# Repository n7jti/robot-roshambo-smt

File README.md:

# robot-roshambo-smt
the SMT board for Robot Rock Paper Scissors

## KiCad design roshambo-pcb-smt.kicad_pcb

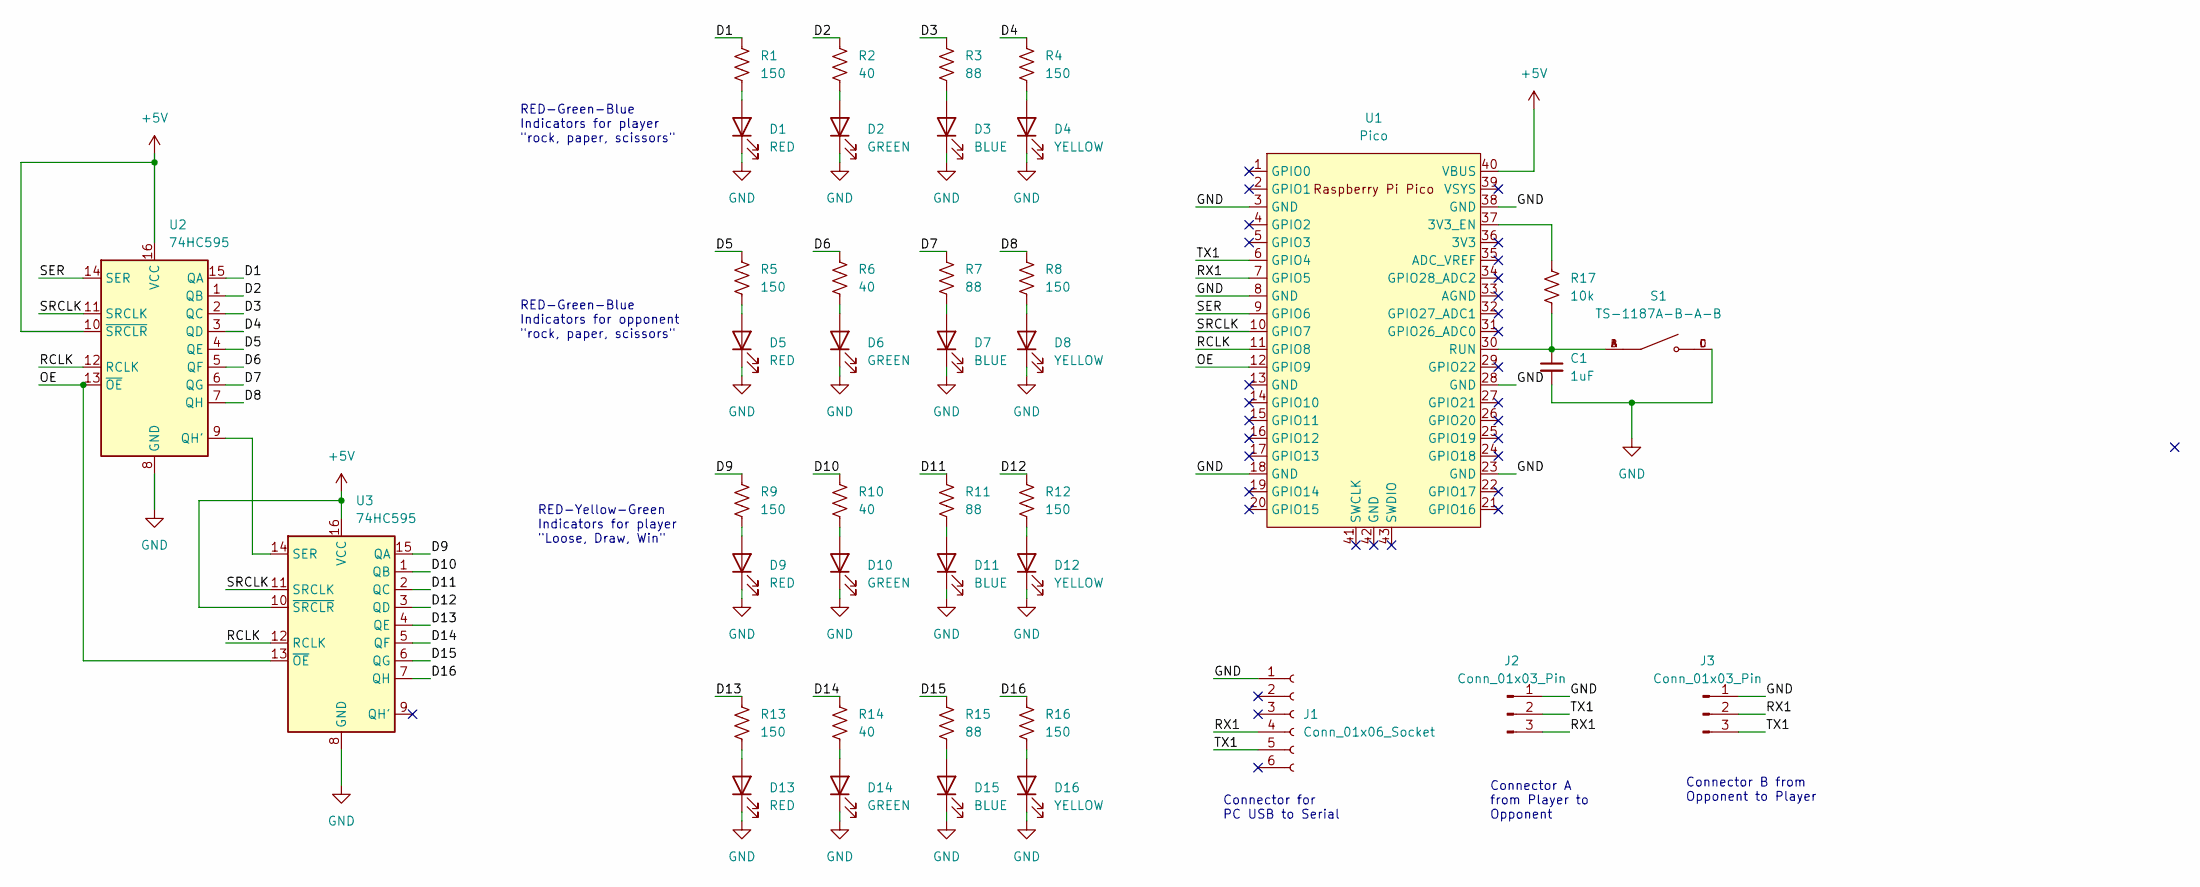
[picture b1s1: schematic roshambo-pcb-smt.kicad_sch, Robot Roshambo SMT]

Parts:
C1: 1uF; C_0603_1608Metric
D1, D5, D9, D13: RED; LED_0603_1608Metric
D2, D6, D10, D14: GREEN; LED_0603_1608Metric
D3, D7, D11, D15: BLUE; LED_0603_1608Metric
D4, D8, D12, D16: YELLOW; LED_0603_1608Metric
J1: Conn_01x06_Socket; PinHeader_1x06_P2.54mm_Vertical
J2, J3: Conn_01x03_Pin; PinHeader_1x03_P2.54mm_Vertical
R1, R4, R5, R8, R9, R12, R13, R16: 150; R_0402_1005Metric
R2, R6, R10, R14: 40; R_0402_1005Metric
R3, R7, R11, R15: 88; R_0402_1005Metric
R17: 10k; R_0402_1005Metric
S1: TS-1187A-B-A-B; SW_TS-1187A-B-A-B; PARTREV A0
U1: Pico; RPi_Pico_SMD_TH
U2, U3: 74HC595; SO-16_3.9x9.9mm_P1.27mm

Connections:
+5V: U1.40 (VBUS), U2.10 (~SRCLR), U2.16 (VCC), U3.10 (~SRCLR), U3.16 (VCC)
/D1: R1.1, U2.15 (QA)
/D2: R2.1, U2.1 (QB)
/D3: R3.1, U2.2 (QC)
/D4: R4.1, U2.3 (QD)
/D5: R5.1, U2.4 (QE)
/D6: R6.1, U2.5 (QF)
/D7: R7.1, U2.6 (QG)
/D8: R8.1, U2.7 (QH)
/D9: R9.1, U3.15 (QA)
/D10: R10.1, U3.1 (QB)
/D11: R11.1, U3.2 (QC)
/D12: R12.1, U3.3 (QD)
/D13: R13.1, U3.4 (QE)
/D14: R14.1, U3.5 (QF)
/D15: R15.1, U3.6 (QG)
/D16: R16.1, U3.7 (QH)
/OE: U1.12 (GPIO9), U2.13 (~OE), U3.13 (~OE)
/RCLK: U1.11 (GPIO8), U2.12 (RCLK), U3.12 (RCLK)
/RX1: J1.4, J2.3, J3.2, U1.7 (GPIO5)
/SER: U1.9 (GPIO6), U2.14 (SER)
/SRCLK: U1.10 (GPIO7), U2.11 (SRCLK), U3.11 (SRCLK)
/TX1: J1.5, J2.2, J3.3, U1.6 (GPIO4)
GND: C1.2, D1.1 (K), D2.1 (K), D3.1 (K), D4.1 (K), D5.1 (K), D6.1 (K), D7.1 (K), D8.1 (K), D9.1 (K), D10.1 (K), D11.1 (K), D12.1 (K), D13.1 (K), D14.1 (K), D15.1 (K), D16.1 (K), J1.1, J2.1, J3.1, S1.C, S1.D, U1.3 (GND), U1.8 (GND), U1.18 (GND), U1.23 (GND), U1.28 (GND), U1.38 (GND), U2.8 (GND), U3.8 (GND)
unnamed: D1.2 (A), R1.2
unnamed: D2.2 (A), R2.2
unnamed: D3.2 (A), R3.2
unnamed: D4.2 (A), R4.2
unnamed: D5.2 (A), R5.2
unnamed: D6.2 (A), R6.2
unnamed: D7.2 (A), R7.2
unnamed: D8.2 (A), R8.2
unnamed: D9.2 (A), R9.2
unnamed: D10.2 (A), R10.2
unnamed: D11.2 (A), R11.2
unnamed: D12.2 (A), R12.2
unnamed: D13.2 (A), R13.2
unnamed: D14.2 (A), R14.2
unnamed: D15.2 (A), R15.2
unnamed: D16.2 (A), R16.2
unnamed: R17.1, U1.37 (3V3_EN)
unnamed: C1.1, R17.2, S1.A, S1.B, U1.30 (RUN)
unnamed: U2.9 (QH'), U3.14 (SER)

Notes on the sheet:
RED-Green-Blue Indicators for player "rock, paper, scissors"
Connector A from Player to Opponent
RED-Yellow-Green Indicators for player "Loose, Draw, Win"
Connector for PC USB to Serial
Connector B from Opponent to Player
RED-Green-Blue Indicators for opponent "rock, paper, scissors"

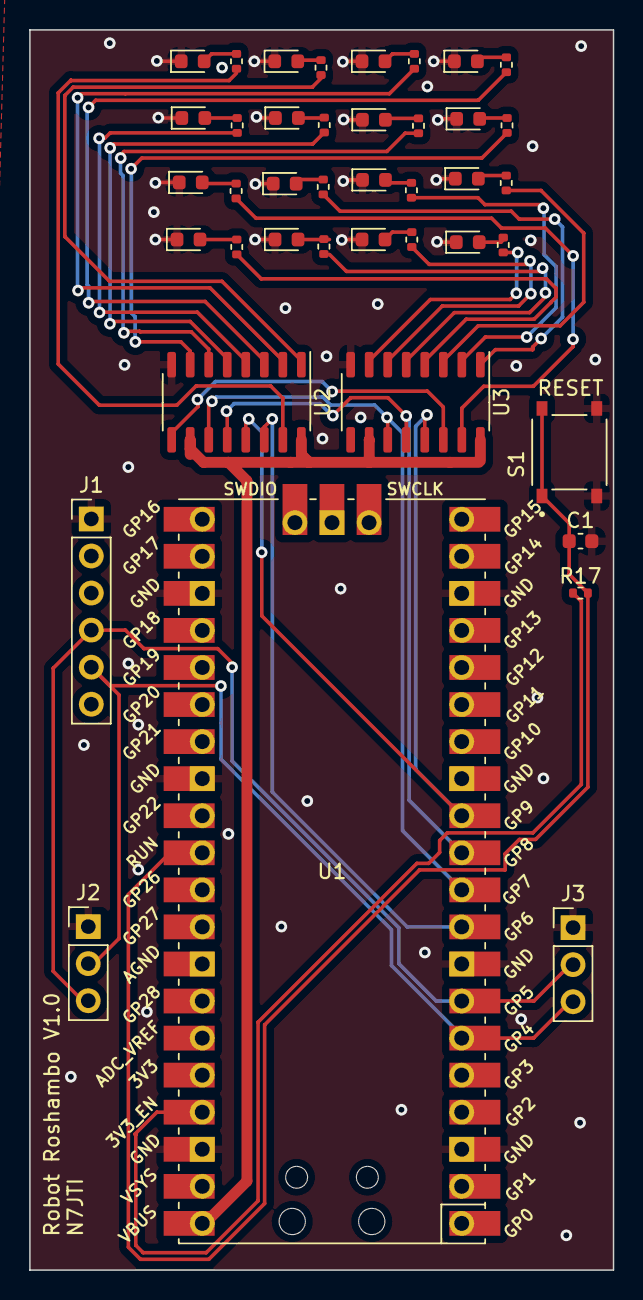
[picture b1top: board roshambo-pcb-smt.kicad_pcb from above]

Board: 2 copper layers, 40.0 x 85.0 mm, 41 parts (0 on the bottom side), 43 nets.

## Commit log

2023-07-09 Add some basic fils
2023-07-10 start layout
2023-07-10 More progress on the layout
2023-07-11 Released to Production
2023-07-11 Production files and datasheets
2023-07-11 Get a PDF version of the schematic
2023-07-16 use 595 shift registers
2023-07-16 Add 595 datasheet
2023-08-02 Add reset switch, OE
2023-08-17 Update Schematic
